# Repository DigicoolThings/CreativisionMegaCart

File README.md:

# CreativisionMegaCart
**NOTE:** *THIS IS NOT COMPATIBLE WITH THE CREATIVISION II WITHOUT MODIFICATION!*

Refer: http://www.madrigaldesign.it/forum/viewtopic.php?f=10&t=330&p=3201#p3201

Multiple ROM Cartridge system for the VTech Creativision, AKA the Dick Smith Wizzard

**Originally by CheshireNoir:**

This is a project I’ve been working on for a while and today I’m pleased to announce the release of our open Source MultiCart system.

Clockmeister kindly gave me all the information from his cart, and gave me permission to release this as Open Source. We both also want to acknowledge and thank the great people over at the Madrigal Design Creativision forums for all their help as well.

My minor contribution was taking the design and putting it in KiCad. I had to spend a bit of time debugging, but Clockmeister assisted above and beyond the call of duty.

This design is released under a CC-BY-SA license. Remix, but always share!

I won’t include ROMs for copyright reasons but they are quite easy to locate on the net if you search around. Note: If you want to program your own EPROM, I understand you have to split the 32K image into two 16K files and then swap the first 16K with the second 16K and re-join them. Clockmeister suggests WinHEX for this.

Parts list is as follows:
* 1x 27C801 EPROM (or equivalent)
* 1x 0.1uF bypass Capacitor
* 2x 1N4148 Diode (or equivalent)
* 1x 5 way DIL Switch (5 switches)
* 1x 6 way 4.7kΩ Resistor Network. (Don’t do what I did and order the 5 way because you counted the pins. It should have seven pins)

**Revised by DigicoolThings (v1.2):**

The CheshireNoir published CreativisionMegaCart project had some observations that I wasn't happy with:-

a) The PCB did not match the Schematic (e.g. Multiple resistors, instead of a single Resistor Network).

b) The 27C801 EPROM had CE (Chip Enable) permanently enabled (tied to GND), which means the chip would always be drawing 35ma, instead of dropping to 0.1ma (in standby).  Normal design practice with a 27C801 EPROM is to utlilise CE for the Chip Select.

c) The PCB routing appeared to have some auto-routing quirks.

d) The bypass capacitor was located distant from the 27C801 power pin.

To resolve the above observations, I have:

a) Replaced the individual resistors on the PCB with a single Resistor Network (as per the schematic).
 
b) Amended the schematic to instead tie together the CE & OE pins to the ROM Chip Select.

c) Manually re-routed the PCB and ground plane (to satisfy my perfectionist tendancies).

d) Relocated the bypass capacitor to be alongside the IC power pin.  Also, relocate the diodes to be alongside each other.

Finally, I also renamed the KiCAD project to be consistent with the repository name.
i.e. The original WizzardCartRPack was renamed to CreativisionMegaCart.
 
Hopefully, these constructive changes are appropriate to the v1.2 increment.

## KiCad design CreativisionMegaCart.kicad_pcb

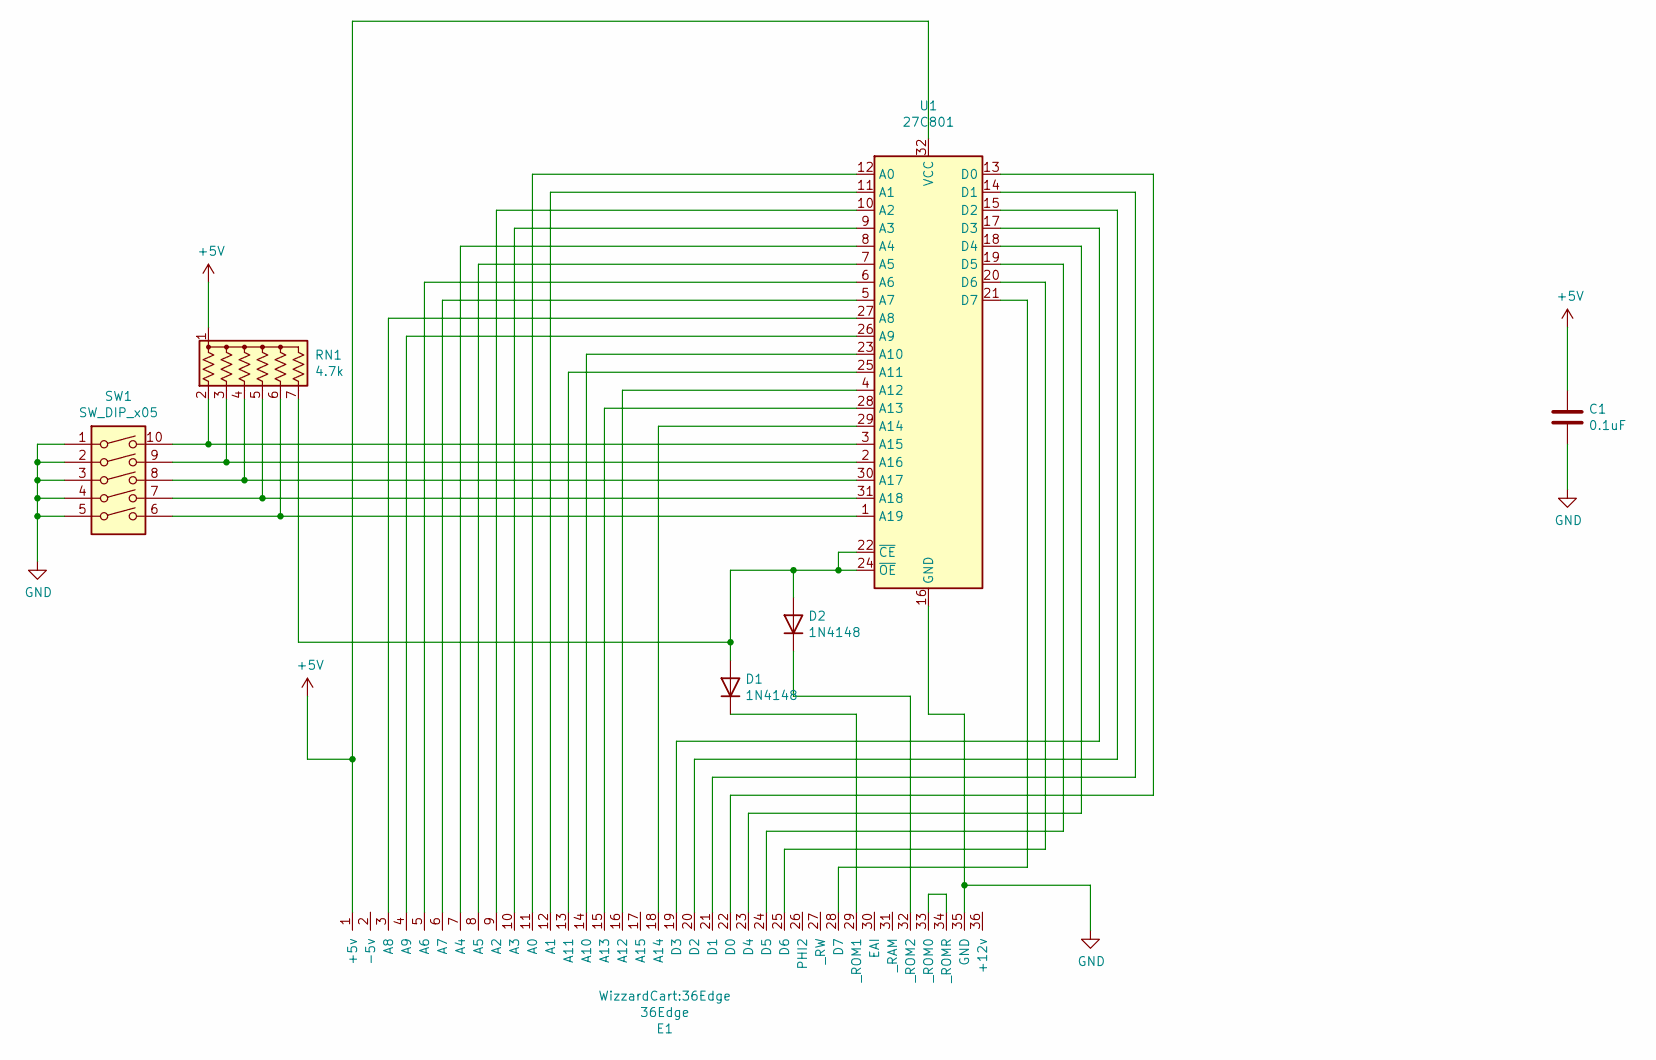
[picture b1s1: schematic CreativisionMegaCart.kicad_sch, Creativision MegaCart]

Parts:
C1: 0.1uF; C_Disc_D8.0mm_W2.5mm_P5.00mm
D1, D2: 1N4148; D_DO-35_SOD27_P7.62mm_Horizontal
E1: 36Edge
RN1: 4.7k; R_Array_SIP7
SW1: SW_DIP_x05; DIP-10_W7.62mm_Socket_LongPads
U1: 27C801; DIP-32_W15.24mm_Socket_LongPads

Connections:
+5V: C1.1, E1.1 (+5v), RN1.1 (common), U1.32 (VCC)
GND: C1.2, E1.35 (GND), SW1.1, SW1.2, SW1.3, SW1.4, SW1.5, U1.16 (GND)
unnamed: D1.2 (A), D2.2 (A), RN1.7 (R6), U1.22 (~CE), U1.24 (~OE)
unnamed: D1.1 (K), E1.29 (_ROM1)
unnamed: D2.1 (K), E1.32 (_ROM2)
unnamed: E1.11 (A0), U1.12 (A0)
unnamed: E1.12 (A1), U1.11 (A1)
unnamed: E1.9 (A2), U1.10 (A2)
unnamed: E1.10 (A3), U1.9 (A3)
unnamed: E1.7 (A4), U1.8 (A4)
unnamed: E1.8 (A5), U1.7 (A5)
unnamed: E1.5 (A6), U1.6 (A6)
unnamed: E1.6 (A7), U1.5 (A7)
unnamed: E1.3 (A8), U1.27 (A8)
unnamed: E1.4 (A9), U1.26 (A9)
unnamed: E1.14 (A10), U1.23 (A10)
unnamed: E1.13 (A11), U1.25 (A11)
unnamed: E1.16 (A12), U1.4 (A12)
unnamed: E1.15 (A13), U1.28 (A13)
unnamed: E1.18 (A14), U1.29 (A14)
unnamed: E1.22 (D0), U1.13 (D0)
unnamed: E1.21 (D1), U1.14 (D1)
unnamed: E1.20 (D2), U1.15 (D2)
unnamed: E1.19 (D3), U1.17 (D3)
unnamed: E1.23 (D4), U1.18 (D4)
unnamed: E1.24 (D5), U1.19 (D5)
unnamed: E1.25 (D6), U1.20 (D6)
unnamed: E1.28 (D7), U1.21 (D7)
unnamed: E1.33 (_ROM0), E1.34 (_ROMR)
unnamed: RN1.2 (R1), SW1.10, U1.3 (A15)
unnamed: RN1.3 (R2), SW1.9, U1.2 (A16)
unnamed: RN1.4 (R3), SW1.8, U1.30 (A17)
unnamed: RN1.5 (R4), SW1.7, U1.31 (A18)
unnamed: RN1.6 (R5), SW1.6, U1.1 (A19)

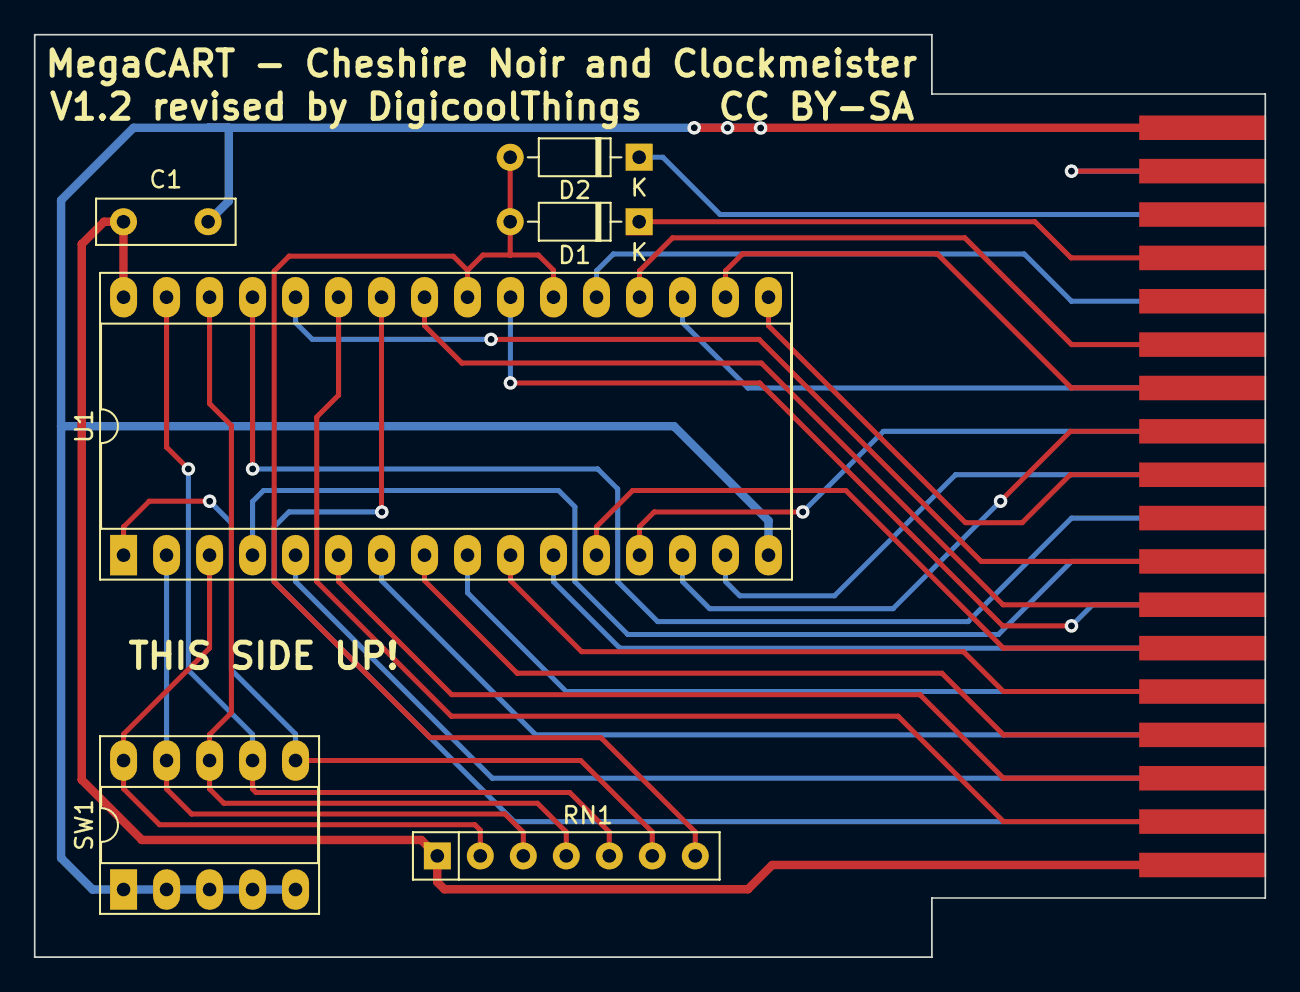
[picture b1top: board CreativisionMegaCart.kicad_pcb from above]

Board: 2 copper layers, 72.7 x 54.5 mm, 7 parts (0 on the bottom side), 34 nets.

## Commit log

2024-08-31 Various changes to take the CreativisionMegaCart design to v1.2. All changes made are as I've documented in the README.md update.
2024-08-31 Add schematic PDF render, and PCB PNG render, for quick viewing / and those without KiCAD installed.
2024-08-31 Update README.md to better format / parts list layout & corrections.

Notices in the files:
CreativisionMegaCart.kicad_pcb:
V1.2 revised by DigicoolThings CC BY-SA
CreativisionMegaCart.kicad_sch:
License: CA BY-SA
